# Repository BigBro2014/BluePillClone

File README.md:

# BluePillClone

A clone of BiluePill board.

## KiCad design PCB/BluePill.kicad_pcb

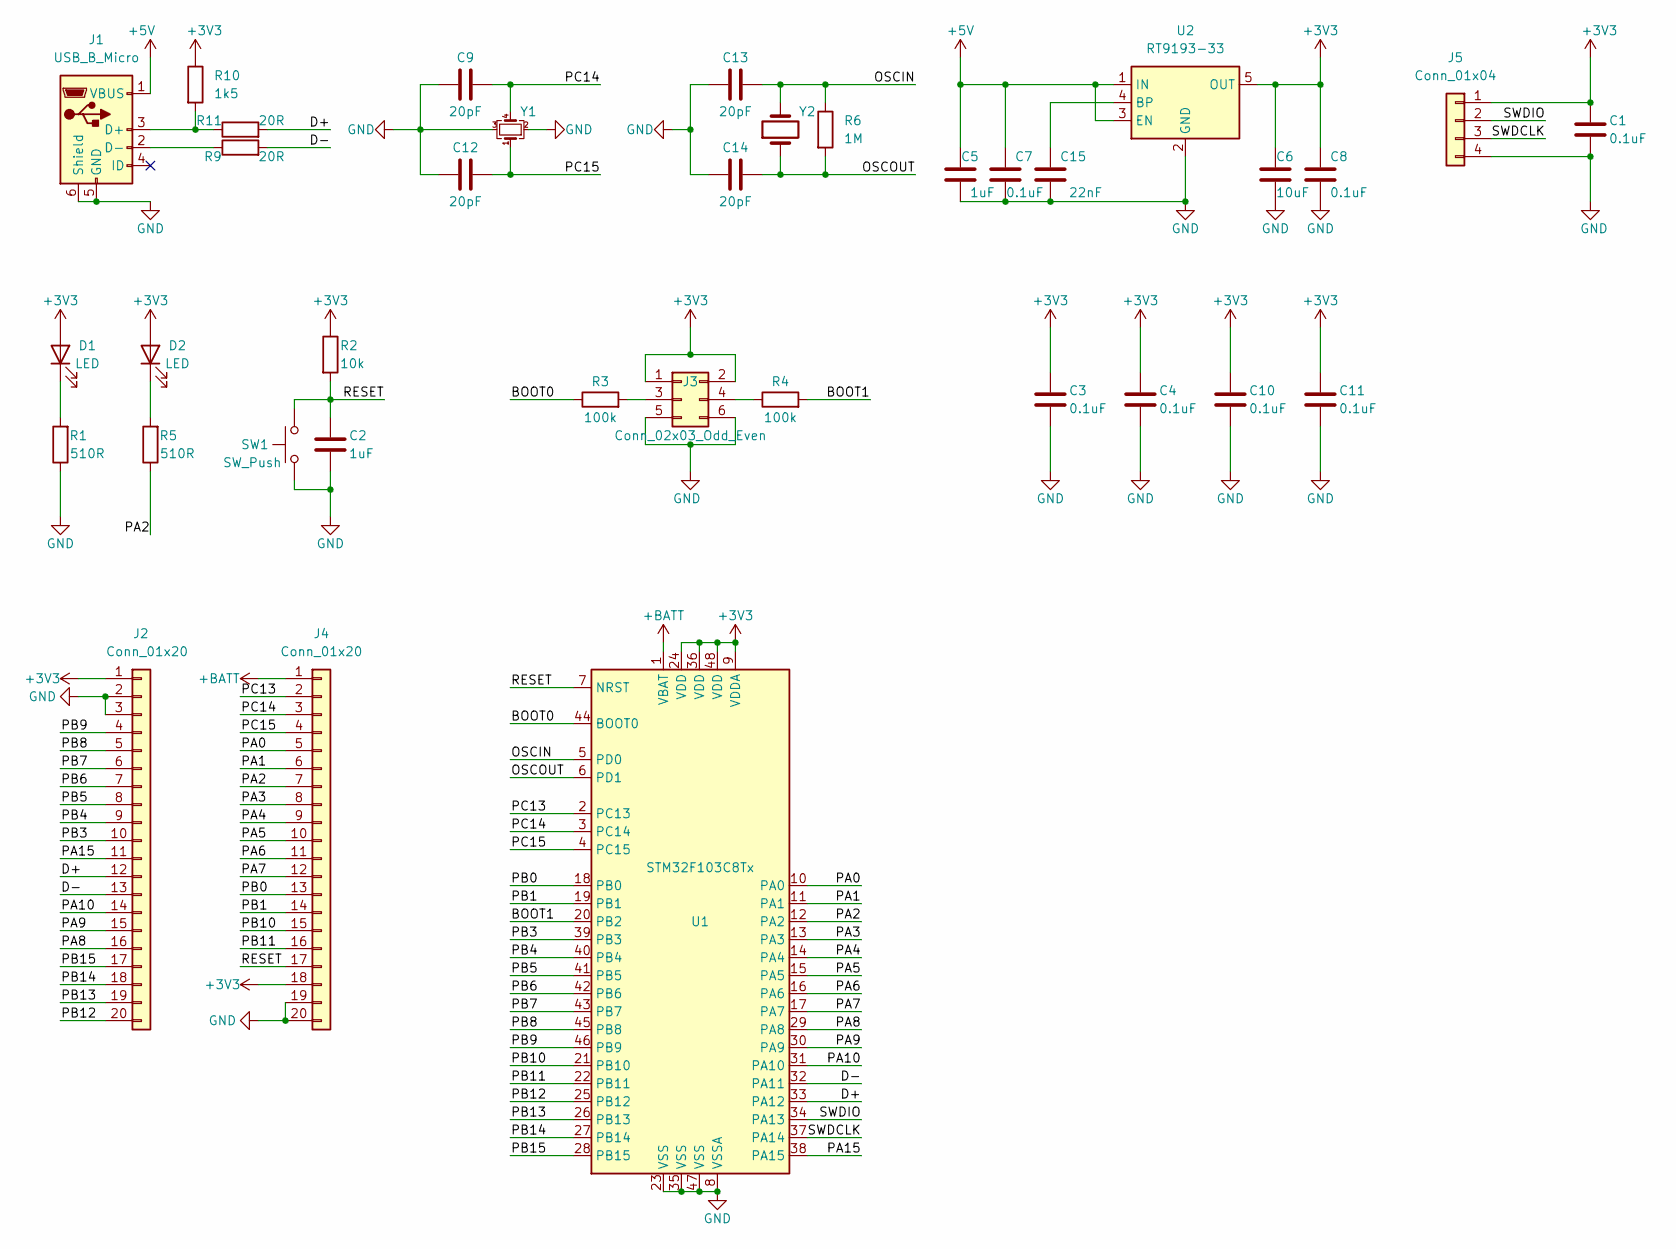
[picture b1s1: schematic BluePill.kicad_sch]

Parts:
C1, C3, C4, C7, C8, C10, C11: 0.1uF; C_0603_1608Metric
C2, C5: 1uF; C_0603_1608Metric
C6: 10uF; C_0603_1608Metric
C9, C12, C13, C14: 20pF; C_0603_1608Metric
C15: 22nF; C_0603_1608Metric
D1, D2: LED; C_0603_1608Metric
J1: USB_B_Micro; USB_Micro-B_Molex-105017-0001
J2, J4: Conn_01x20; PinHeader_1x20_P2.54mm_Vertical
J3: Conn_02x03_Odd_Even; PinHeader_2x03_P2.54mm_Vertical
J5: Conn_01x04; PinHeader_1x04_P2.54mm_Horizontal
R1, R5: 510R; C_0603_1608Metric
R2: 10k; C_0603_1608Metric
R3, R4: 100k; C_0603_1608Metric
R6: 1M; C_0603_1608Metric
R9, R11: 20R; C_0603_1608Metric
R10: 1k5; C_0603_1608Metric
SW1: SW_Push; SW_SPST_B3U-1000P
U1: STM32F103C8Tx; LQFP-48_7x7mm_P0.5mm
U2: RT9193-33; SOT-23-5
Y1: (no value)
Y2: 8MHZ; Crystal_HC49-4H_Vertical

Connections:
+3V3: C1.1, C3.1, C4.1, C6.1, C8.1, C10.1, C11.1, D1.2 (A), D2.2 (A), J2.1, J3.1, J3.2, J4.18, J5.1, R2.1, R10.1, U1.9 (VDDA), U1.24 (VDD), U1.36 (VDD), U1.48 (VDD), U2.5 (OUT)
+5V: C5.2, C7.1, J1.1 (VBUS), U2.1 (IN), U2.3 (EN)
+BATT: J4.1, U1.1 (VBAT)
/BOOT0: R3.1, U1.44 (BOOT0)
/BOOT1: R4.2, U1.20 (PB2)
/D+: J2.12, R11.2, U1.33 (PA12)
/D-: J2.13, R9.2, U1.32 (PA11)
/OSCIN: C13.2, R6.1, U1.5 (PD0), Y2.2
/OSCOUT: C14.2, R6.2, U1.6 (PD1), Y2.1
/PA0: J4.5, U1.10 (PA0)
/PA1: J4.6, U1.11 (PA1)
/PA2: J4.7, R5.1, U1.12 (PA2)
/PA3: J4.8, U1.13 (PA3)
/PA4: J4.9, U1.14 (PA4)
/PA5: J4.10, U1.15 (PA5)
/PA6: J4.11, U1.16 (PA6)
/PA7: J4.12, U1.17 (PA7)
/PA8: J2.16, U1.29 (PA8)
/PA9: J2.15, U1.30 (PA9)
/PA10: J2.14, U1.31 (PA10)
/PA15: J2.11, U1.38 (PA15)
/PB0: J4.13, U1.18 (PB0)
/PB1: J4.14, U1.19 (PB1)
/PB3: J2.10, U1.39 (PB3)
/PB4: J2.9, U1.40 (PB4)
/PB5: J2.8, U1.41 (PB5)
/PB6: J2.7, U1.42 (PB6)
/PB7: J2.6, U1.43 (PB7)
/PB8: J2.5, U1.45 (PB8)
/PB9: J2.4, U1.46 (PB9)
/PB10: J4.15, U1.21 (PB10)
/PB11: J4.16, U1.22 (PB11)
/PB12: J2.20, U1.25 (PB12)
/PB13: J2.19, U1.26 (PB13)
/PB14: J2.18, U1.27 (PB14)
/PB15: J2.17, U1.28 (PB15)
/PC13: J4.2, U1.2 (PC13)
/PC14: C9.2, J4.3, U1.3 (PC14), Y1.4
/PC15: C12.1, J4.4, U1.4 (PC15), Y1.1
/RESET: C2.1, J4.17, R2.2, SW1.2, U1.7 (NRST)
/SWDCLK: J5.3, U1.37 (PA14)
/SWDIO: J5.2, U1.34 (PA13)
GND: C1.2, C2.2, C3.2, C4.2, C5.1, C6.2, C7.2, C8.2, C9.1, C10.2, C11.2, C12.2, C13.1, C14.1, C15.2, J1.5 (GND), J1.6 (Shield), J2.2, J2.3, J3.5, J3.6, J4.19, J4.20, J5.4, R1.1, SW1.1, U1.8 (VSSA), U1.23 (VSS), U1.35 (VSS), U1.47 (VSS), U2.2 (GND), Y1.2, Y1.3
unnamed: C15.1, U2.4 (BP)
unnamed: D1.1 (K), R1.2
unnamed: D2.1 (K), R5.2
unnamed: J1.2 (D-), R9.1
unnamed: J1.3 (D+), R10.2, R11.1
unnamed: J3.3, R3.2
unnamed: J3.4, R4.1

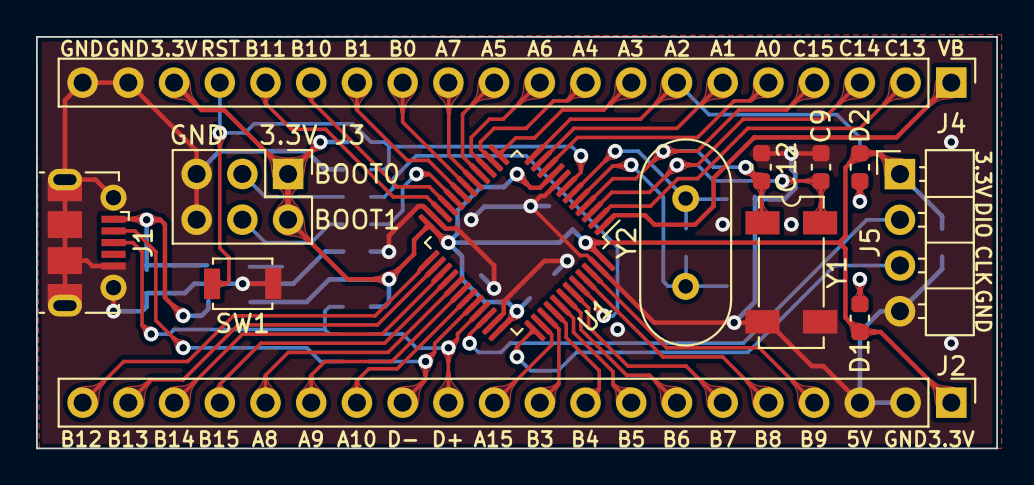
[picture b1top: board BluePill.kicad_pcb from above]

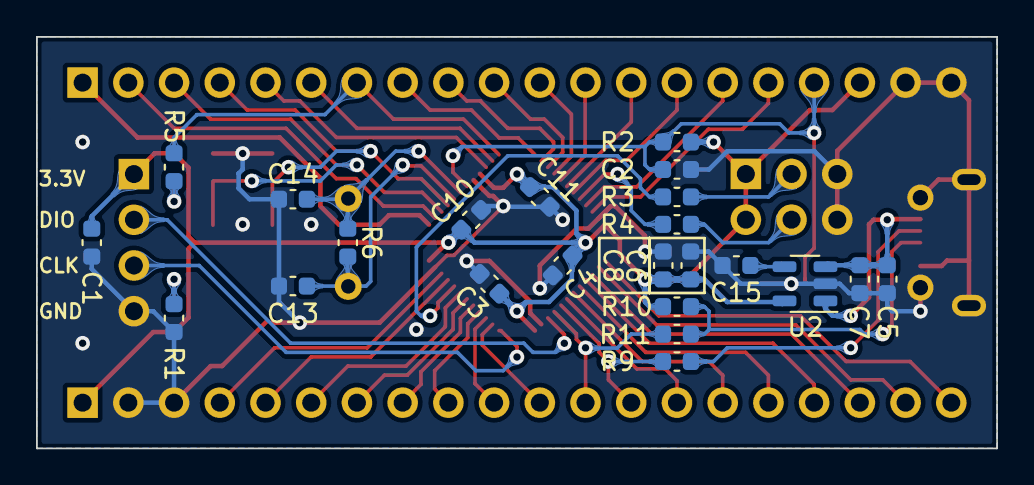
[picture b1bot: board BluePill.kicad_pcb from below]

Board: 2 copper layers, 53.3 x 22.9 mm, 36 parts (23 on the bottom side), 50 nets.

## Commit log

2022-04-07 周冰完成修改
2022-04-08 Add README.md
2022-04-08 更换USB插座封装
2022-04-29 修复32K晶振问题；局部优化。
